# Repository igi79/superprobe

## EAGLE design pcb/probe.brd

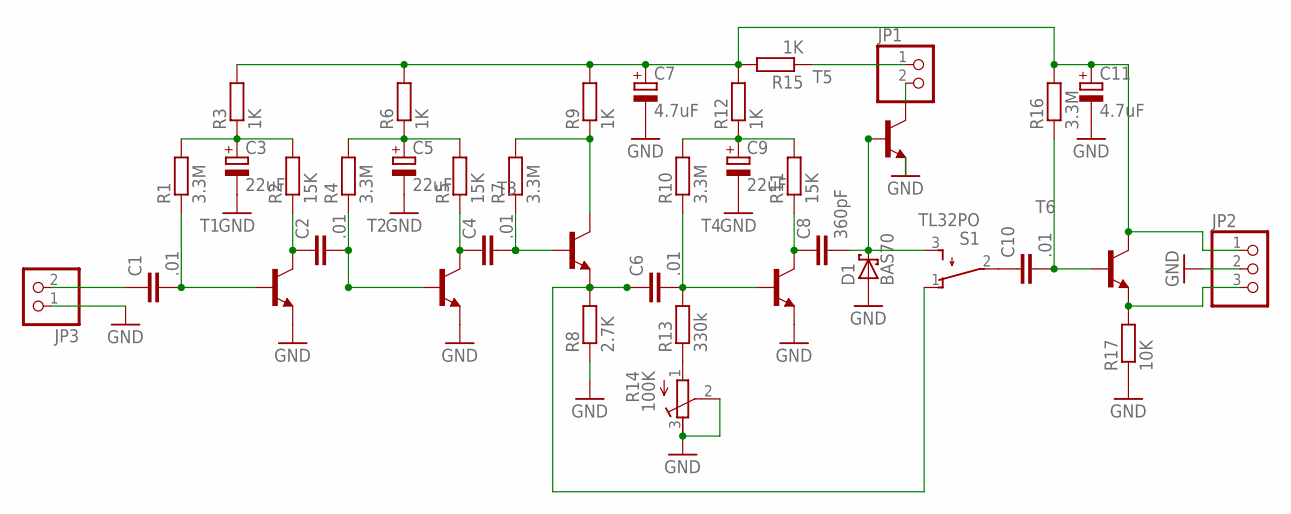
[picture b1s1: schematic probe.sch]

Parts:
C1, C2, C4, C6, C10: .01; C0603
C3, C5, C9: 22uF; CT3528
C7, C11: 4.7uF; CT3528
C8: 360pF; C0603
D1: BAS70; SOT23
JP1, JP3: PINHD-1X2; 1X02
JP2: PINHD-1X3; 1X03
R1, R4, R7, R10, R16: 3.3M; R0603
R2, R5, R11: 15K; R0603
R3, R6, R9, R12, R15: 1K; R0603
R8: 2.7K; R0603
R13: 330k; R0603
R14: 100K; RTRIM3103
R17: 10K; R0603
S1: TL32PO; TL3XPO
T1, T2, T3, T4, T5, T6: BC848-NPN-SOT23-BEC; SOT23-BEC

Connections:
GND: C3.-, C5.-, C7.-, C9.-, C11.-, D1.1 (A), JP2.2, JP3.1, R8.1, R14.2 (S), R14.3 (E), R17.1, T1.E, T2.E, T4.E, T5.E
unnamed: C1.2, R1.1, T1.B
unnamed: C2.1, R2.1, T1.C
unnamed: C3.+, R1.2, R2.2, R3.1
unnamed: C2.2, R4.1, T2.B
unnamed: C4.1, R5.1, T2.C
unnamed: C5.+, R4.2, R5.2, R6.1
unnamed: C4.2, R7.1, T3.B
unnamed: R7.2, R9.1, T3.C
unnamed: C6.1, R8.2, S1.1 (O), T3.E
unnamed: C6.2, R10.1, R13.2, T4.B
unnamed: C8.1, R11.1, T4.C
unnamed: C9.+, R10.2, R11.2, R12.1
unnamed: R13.1, R14.1 (A)
unnamed: JP1.1, R15.1
unnamed: C1.1, JP3.2
unnamed: C8.2, D1.3 (C), S1.3 (S), T5.B
unnamed: C7.+, C11.+, JP2.1, R3.2, R6.2, R9.2, R12.2, R15.2, R16.2, T6.C
unnamed: C10.2, R16.1, T6.B
unnamed: C10.1, S1.2
unnamed: JP2.3, R17.2, T6.E
unnamed: JP1.2, T5.C

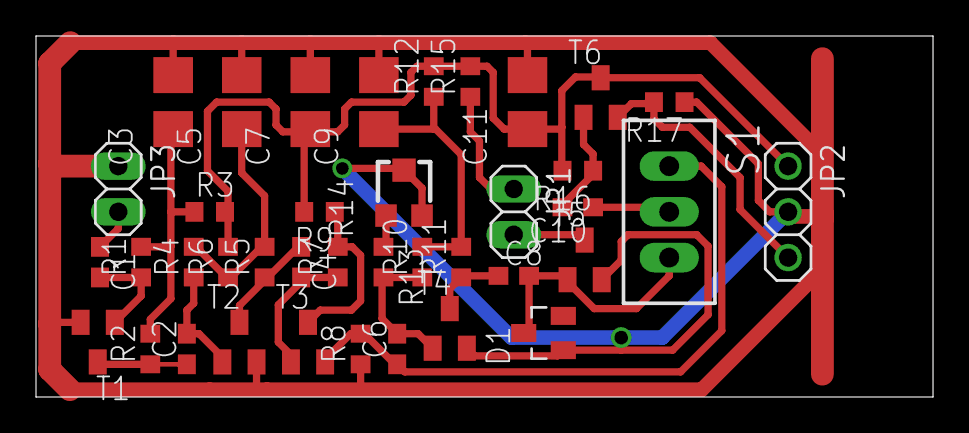
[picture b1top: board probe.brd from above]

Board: 2 copper layers, 49.8 x 20.1 mm, 39 parts (0 on the bottom side), 22 nets.

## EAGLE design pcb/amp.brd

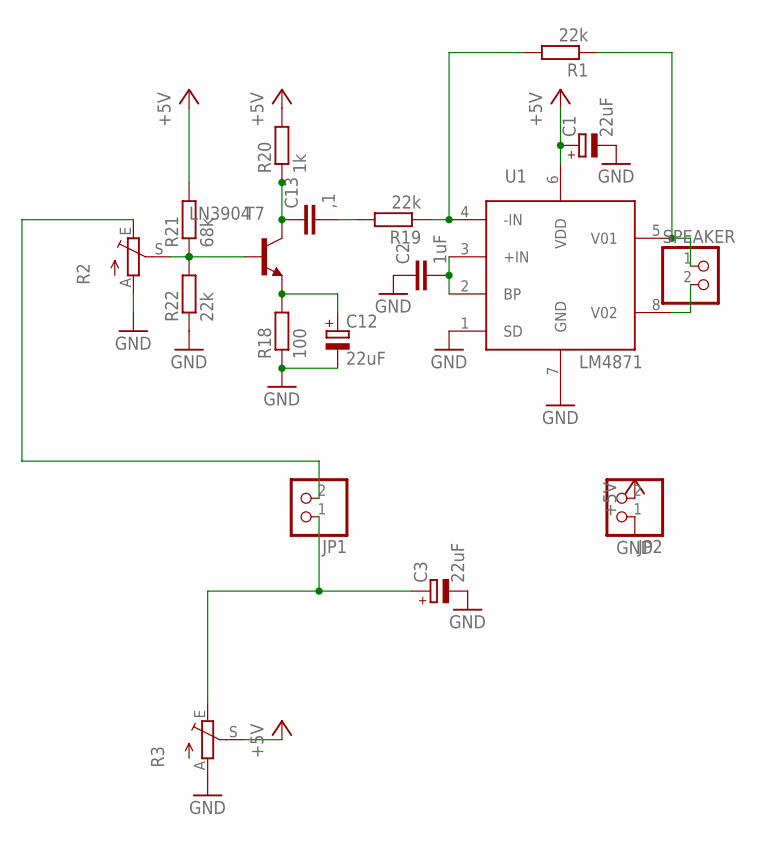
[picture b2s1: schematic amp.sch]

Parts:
C1, C3, C12: 22uF; CT3528
C2: 1uF; C0603
C13: ,1; C0603
JP1, JP2: PINHD-1X2; 1X02
R1, R19, R22: 22k; R0603
R2, R3: TRIM_EU-LI15; LI15
R18: 100; R0603
R20: 1k; R0603
R21: 68k; R0603
SPEAKER: PINHD-1X2; 1X02
T7: LN3904; SOT23-BEC
U1: LM4871; ICS_SOP08

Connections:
+5V: C1.+, JP2.2, R3.S, R20.2, R21.2, U1.6 (VDD)
GND: C1.-, C2.1, C3.-, C12.-, JP2.1, R2.A, R3.A, R18.1, R22.1, U1.1 (SD), U1.7 (GND)
unnamed: R1.2, R19.1, U1.4 (-IN)
unnamed: C2.2, U1.2 (BP), U1.3 (+IN)
unnamed: R1.1, SPEAKER.1, U1.5 (V01)
unnamed: SPEAKER.2, U1.8 (V02)
unnamed: JP1.2, R2.E
unnamed: C3.+, JP1.1, R3.E
unnamed: C12.+, R18.2, T7.E
unnamed: C13.1, R20.1, T7.C
unnamed: C13.2, R19.2
unnamed: R2.S, R21.1, R22.2, T7.B

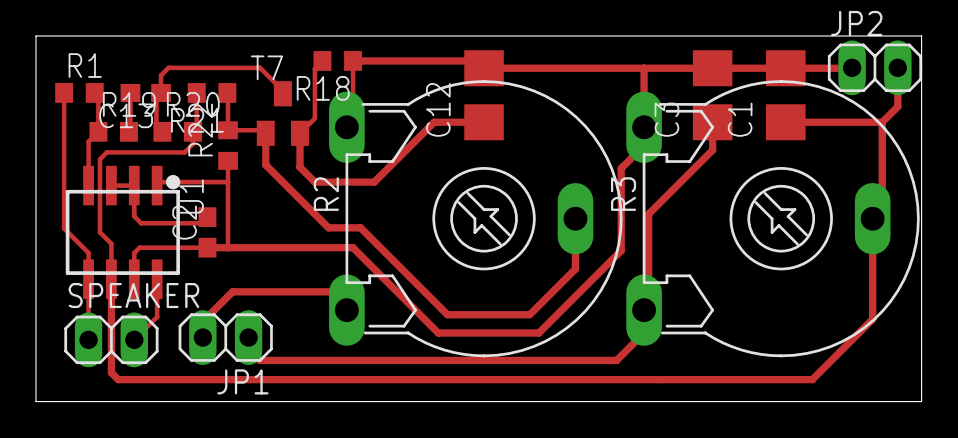
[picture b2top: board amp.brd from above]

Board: 2 copper layers, 49.2 x 20.3 mm, 18 parts (0 on the bottom side), 12 nets.

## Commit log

2020-10-17 init
